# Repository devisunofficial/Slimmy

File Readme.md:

# Slimmy

Slimmy is a Unidirectional USB 3.0 TF-Card Reader.
1. Why I made this?
   Because I wanted to make Type-C USB 3.0 device.
2. Why Unidirectional?
   Routing biderctional Type-C is difficult(atleast for me) and it would further increase the fabrication cost

### Features:

 - USB 3.0 TF-Card Reader
 - True USB 3.0 controller is used

### CAD Model:
Even though there is no Case or anything, here is PCB in 3d View

### PCB:
Here's my PCB! It was made in KiCad. 

Schematic : 
PCB Footprint : 

### Firmware Overview:
No FIRMWARE ;)

### Assembly :
Done By JLCPCB because I don't have Hot plate!!

### BOM Table
|Name|Use|Quantity|Distributer|
|-----|---|-------|-----------|
|GL3224-OIY04|USB Hub Controller|1|JLCPCB|
|PCB|Main-Circuit|1|JLCPCB|
|USB-C|Up-Stream Port|1|JLCPCB|
|TF Card|I don't have TF Card to use USB 3.0|1|Amazon|

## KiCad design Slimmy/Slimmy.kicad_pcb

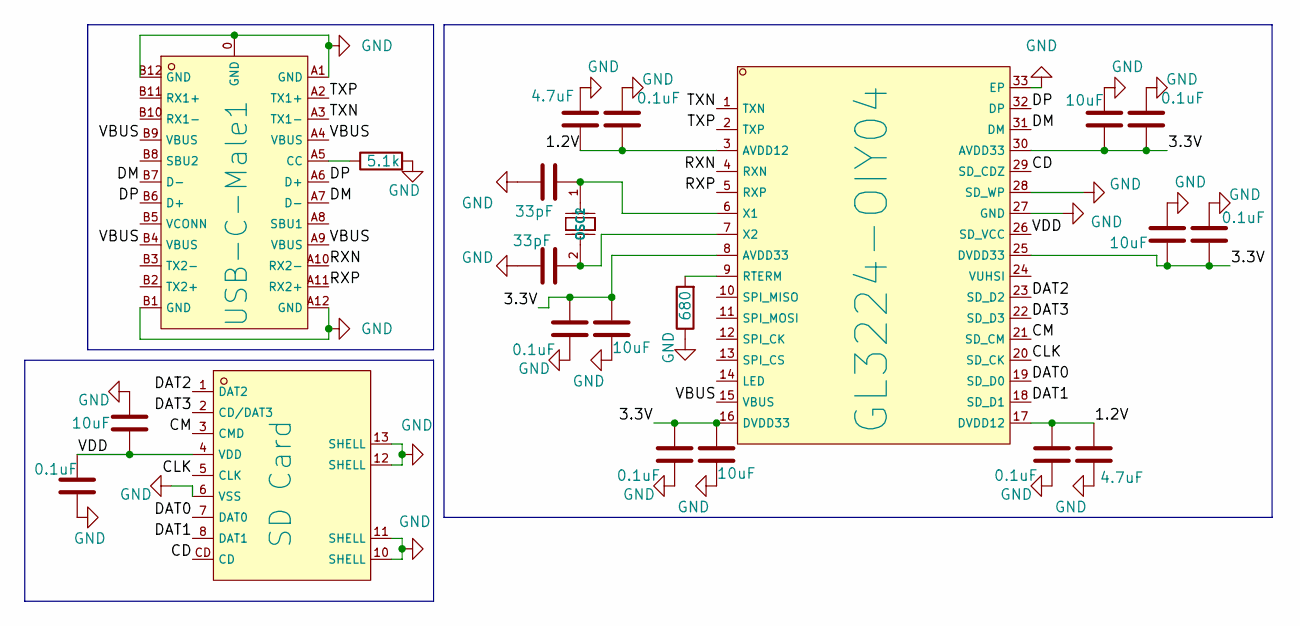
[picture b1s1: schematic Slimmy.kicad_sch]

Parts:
C1, C6, C7, C9, C11, C13, C15: 0.1uF; C_0603_1608Metric
C2, C5, C8, C10, C12: 10uF; C_0603_1608Metric
C3, C4: 33pF; C_0603_1608Metric
C14, C16: 4.7uF; C_0603_1608Metric
R1: 5.1k; R_0805_2012Metric
R2: 680; R_0805_2012Metric
U1: GL3224-OIY04; C157357_HQFN-32_L5_0-W5_0-P0_50-BL-EP3_0; LCSC C157357
U2: SD Card; C5184837_TF-SMD_TF-PUSH; LCSC C5184837
USB-C-Male1: TYPE-C-31-G-02; C530606_USB-C-SMD_TYPE-C-31-G-02; LCSC C530606
X1: HC-49SMD 25MHZ 20PF 20PPM; C14872_HC-49S_L11_4-W4_8; LCSC C14872

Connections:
/1.2V: C13.1, C14.2, C15.1, C16.2, U1.3 (AVDD12), U1.17 (DVDD12)
/3.3V: C5.2, C6.1, C7.1, C8.2, C9.1, C10.2, C11.1, C12.2, U1.8 (AVDD33), U1.16 (DVDD33), U1.25 (DVDD33), U1.30 (AVDD33)
/CD: U1.29 (SD_CDZ), U2.CD
/CLK: U1.20 (SD_CK), U2.5 (CLK)
/CM: U1.21 (SD_CM), U2.3 (CMD)
/DAT0: U1.19 (SD_D0), U2.7 (DAT0)
/DAT1: U1.18 (SD_D1), U2.8 (DAT1)
/DAT2: U1.23 (SD_D2), U2.1 (DAT2)
/DAT3: U1.22 (SD_D3), U2.2 (CD/DAT3)
/DM: U1.31 (DM), USB-C-Male1.A7 (D-), USB-C-Male1.B7 (D-)
/DP: U1.32 (DP), USB-C-Male1.A6 (D+), USB-C-Male1.B6 (D+)
/RXN: U1.4 (RXN), USB-C-Male1.A10 (RX2-)
/RXP: U1.5 (RXP), USB-C-Male1.A11 (RX2+)
/TXN: U1.1 (TXN), USB-C-Male1.A3 (TX1-)
/TXP: U1.2 (TXP), USB-C-Male1.A2 (TX1+)
/VBUS: U1.15 (VBUS), USB-C-Male1.A4 (VBUS), USB-C-Male1.A9 (VBUS), USB-C-Male1.B4 (VBUS), USB-C-Male1.B9 (VBUS)
/VDD: C1.1, C2.2, U1.26 (SD_VCC), U2.4 (VDD)
GND: C1.2, C2.1, C3.1, C4.1, C5.1, C6.2, C7.2, C8.1, C9.2, C10.1, C11.2, C12.1, C13.2, C14.1, C15.2, C16.1, R1.2, R2.1, U1.27 (GND), U1.28 (SD_WP), U1.33 (EP), U2.6 (VSS), U2.10 (SHELL), U2.11 (SHELL), U2.12 (SHELL), U2.13 (SHELL), USB-C-Male1.0 (GND), USB-C-Male1.A1 (GND), USB-C-Male1.A12 (GND), USB-C-Male1.B1 (GND), USB-C-Male1.B12 (GND)
unnamed: R2.2, U1.9 (RTERM)
unnamed: C3.2, U1.6 (X1), X1.1 (OSC1)
unnamed: C4.2, U1.7 (X2), X1.2 (OSC2)
unnamed: R1.1, USB-C-Male1.A5 (CC)

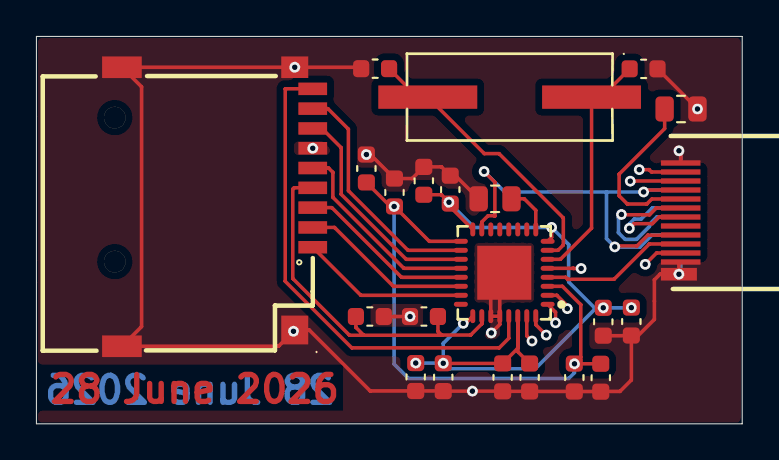
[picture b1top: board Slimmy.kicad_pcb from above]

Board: 4 copper layers, 39.2 x 21.5 mm, 22 parts (0 on the bottom side), 22 nets.

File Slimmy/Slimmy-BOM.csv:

"Id";"Designator";"Footprint";"Quantity";"Designation";"Supplier and ref";
1;"C1, C6, C7, C9, C11, C13, C15";"C_0603_1608Metric";7;"0.1uF";;;
2;"C2, C5, C8, C10, C12";"C_0603_1608Metric";5;"10uF";;;
3;"C3, C4";"C_0603_1608Metric";2;"33pF";;;
4;"C14, C16";"C_0603_1608Metric";2;"4.7uF";;;
5;"R1";"R_0805_2012Metric";1;"5.1k";;;
6;"R2";"R_0805_2012Metric";1;"680";;;
7;"U1";"C157357_HQFN-32_L5_0-W5_0-P0_50-BL-EP3_0";1;"GL3224-OIY04";;;
8;"U2";"C5184837_TF-SMD_TF-PUSH";1;"SD Card";;;
9;"USB-C-Male1";"C530606_USB-C-SMD_TYPE-C-31-G-02";1;"TYPE-C-31-G-02";;;
10;"X1";"C14872_HC-49S_L11_4-W4_8";1;"HC-49SMD 25MHZ 20PF 20PPM";;;

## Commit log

2026-06-28 First
2026-06-28 Final
2026-06-28 Edited Readme
